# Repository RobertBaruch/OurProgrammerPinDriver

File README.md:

# OurProgrammerPinDriver
Pin driver schematic and PCB for OurProgrammer

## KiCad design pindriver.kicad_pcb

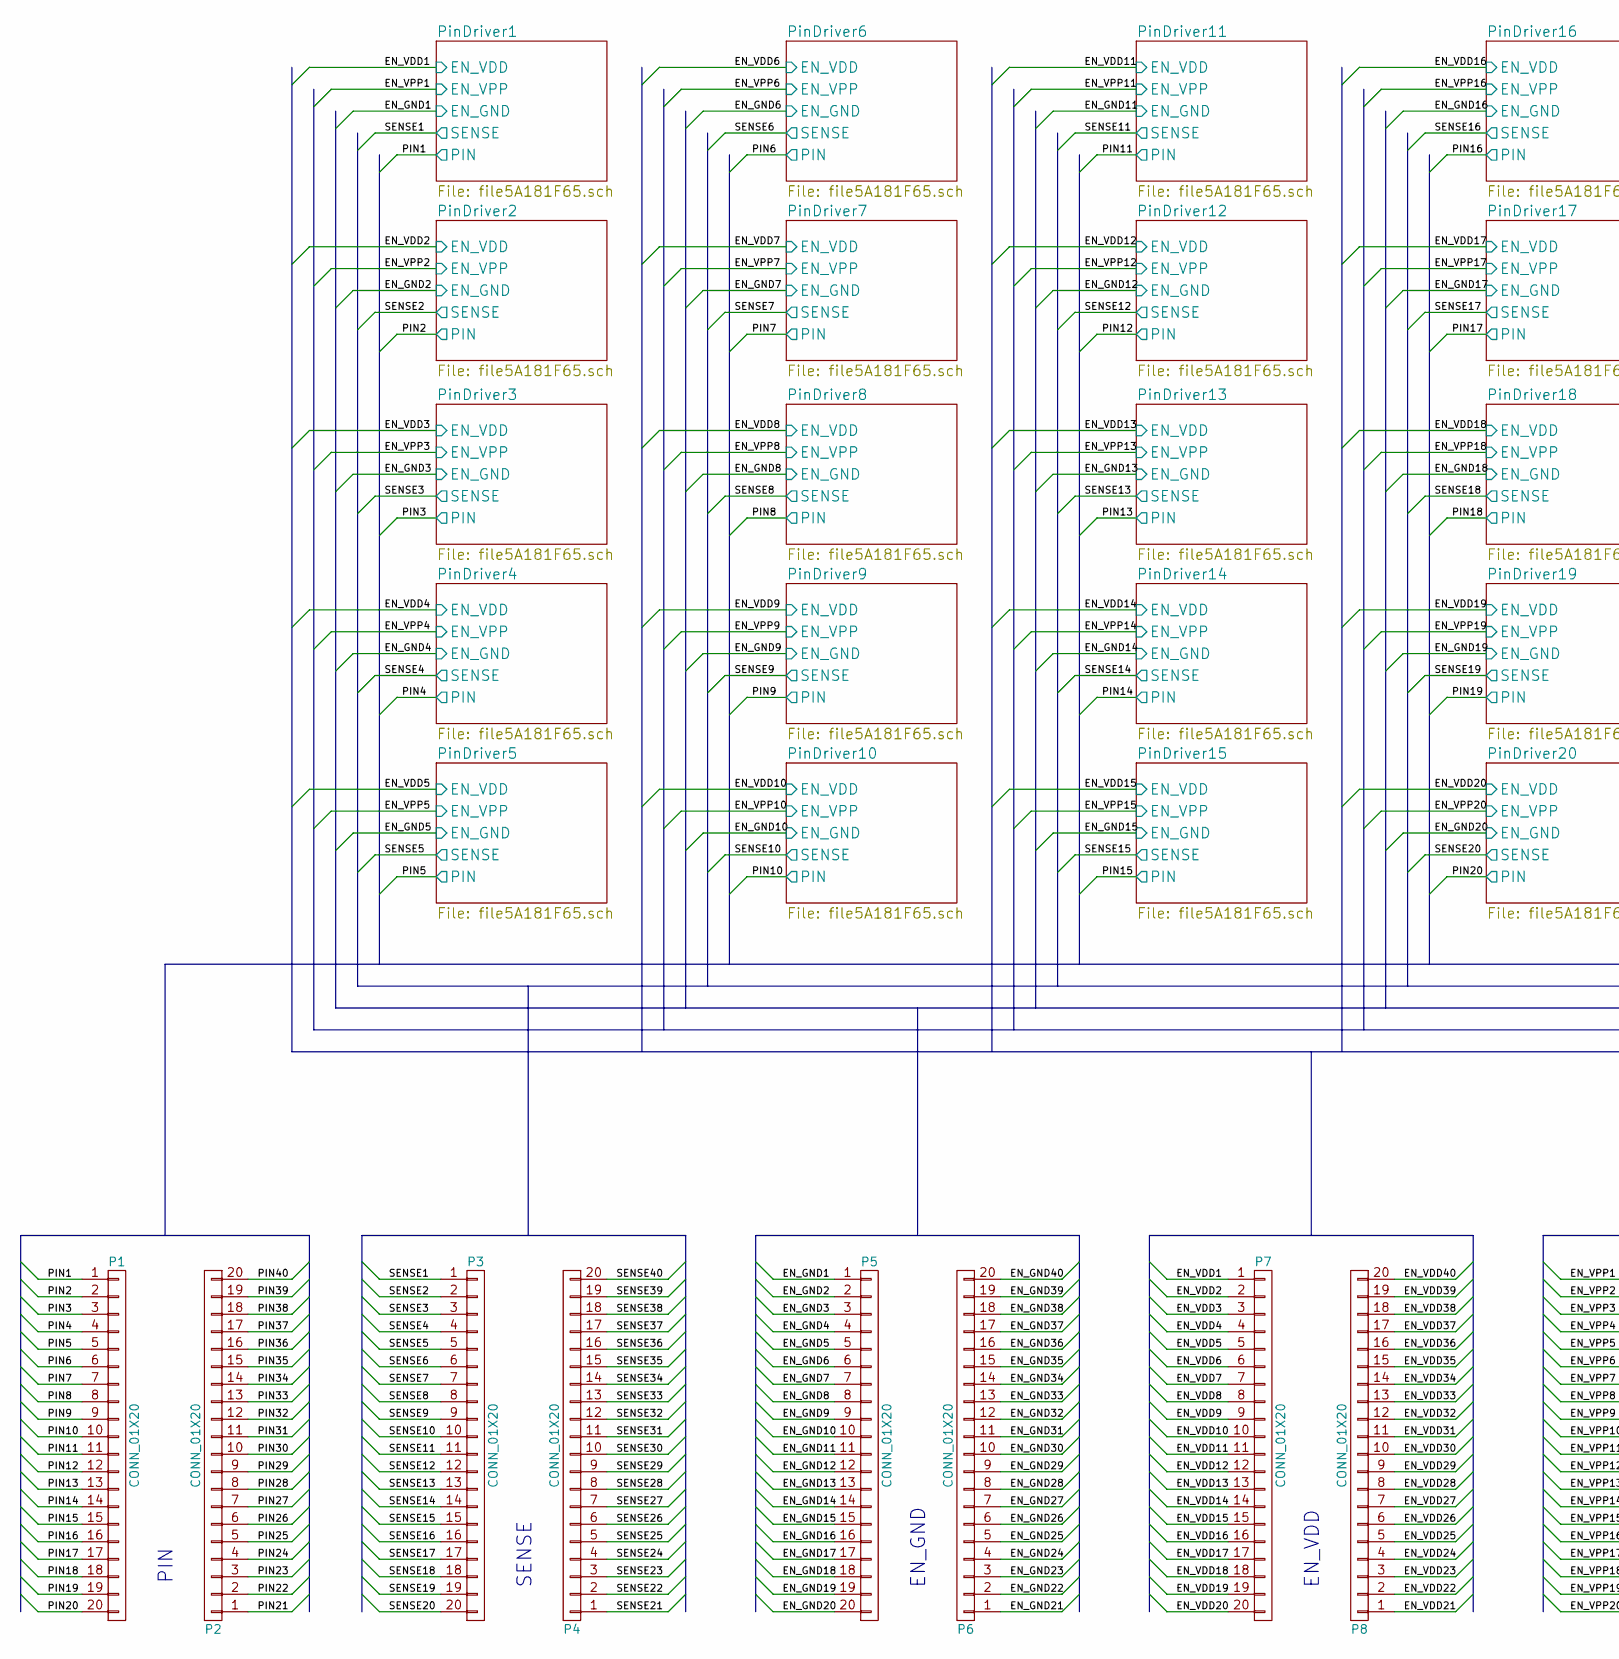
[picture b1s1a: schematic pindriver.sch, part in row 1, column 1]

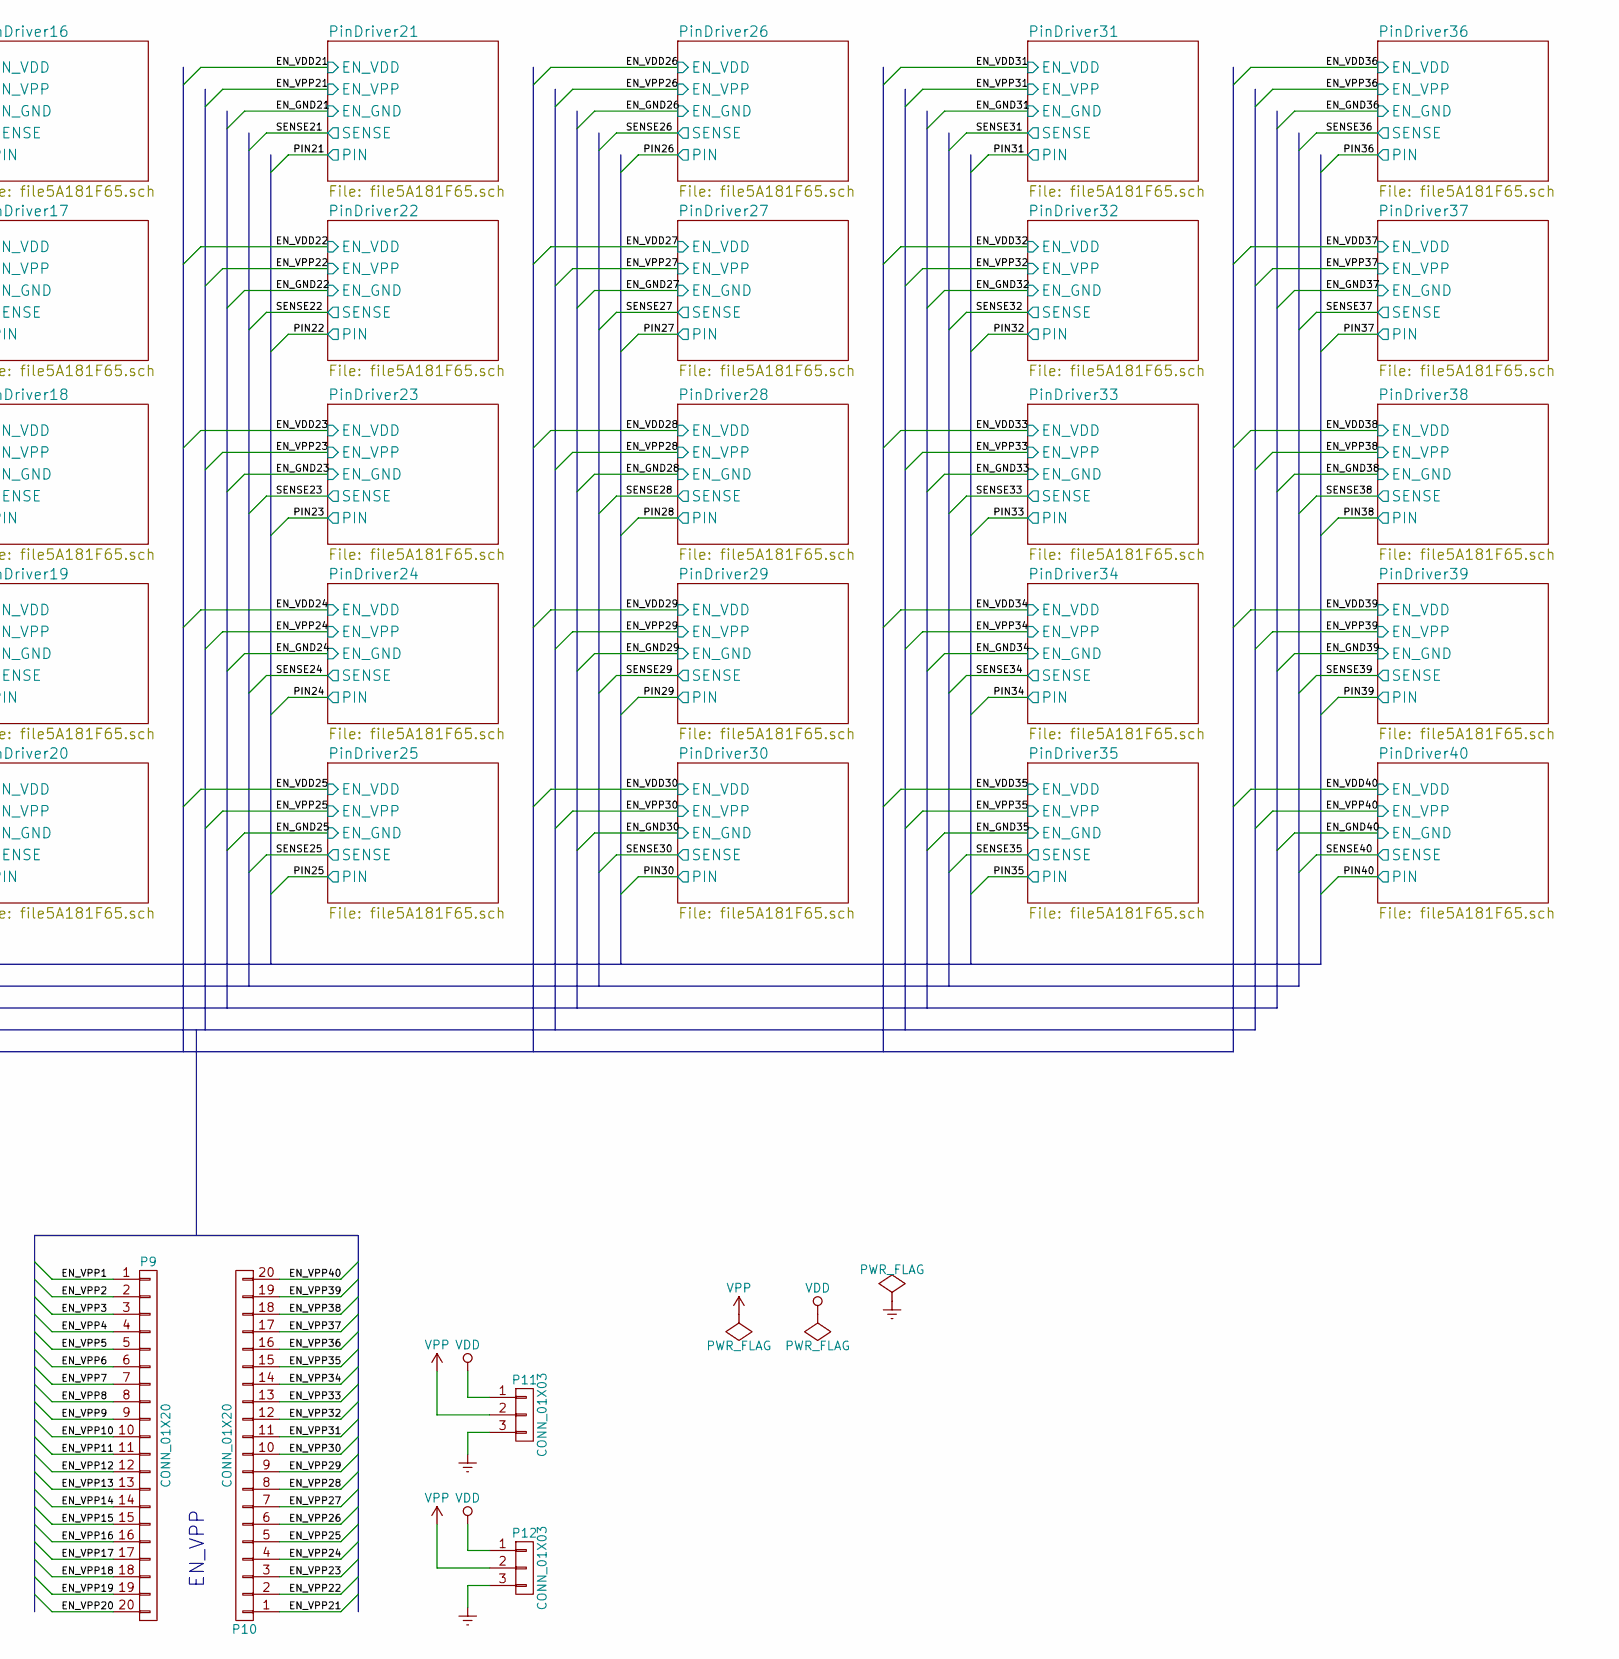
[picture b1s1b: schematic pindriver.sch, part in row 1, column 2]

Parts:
P1, P2, P3, P4, P5, P6, P7, P8, P9, P10: CONN_01X20; SL-120-X-XX_1x20
P11, P12: CONN_01X03; SL-103-X-XX_1x03

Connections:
/EN_GND1: P5.1; also elsewhere on the board
/EN_GND2: P5.2; also elsewhere on the board
/EN_GND3: P5.3; also elsewhere on the board
/EN_GND4: P5.4; also elsewhere on the board
/EN_GND5: P5.5; also elsewhere on the board
/EN_GND6: P5.6; also elsewhere on the board
/EN_GND7: P5.7; also elsewhere on the board
/EN_GND8: P5.8; also elsewhere on the board
/EN_GND9: P5.9; also elsewhere on the board
/EN_GND10: P5.10; also elsewhere on the board
/EN_GND11: P5.11; also elsewhere on the board
/EN_GND12: P5.12; also elsewhere on the board
/EN_GND13: P5.13; also elsewhere on the board
/EN_GND14: P5.14; also elsewhere on the board
/EN_GND15: P5.15; also elsewhere on the board
/EN_GND16: P5.16; also elsewhere on the board
/EN_GND17: P5.17; also elsewhere on the board
/EN_GND18: P5.18; also elsewhere on the board
/EN_GND19: P5.19; also elsewhere on the board
/EN_GND20: P5.20; also elsewhere on the board
/EN_GND21: P6.1; also elsewhere on the board
/EN_GND22: P6.2; also elsewhere on the board
/EN_GND23: P6.3; also elsewhere on the board
/EN_GND24: P6.4; also elsewhere on the board
/EN_GND25: P6.5; also elsewhere on the board
/EN_GND26: P6.6; also elsewhere on the board
/EN_GND27: P6.7; also elsewhere on the board
/EN_GND28: P6.8; also elsewhere on the board
/EN_GND29: P6.9; also elsewhere on the board
/EN_GND30: P6.10; also elsewhere on the board
/EN_GND31: P6.11; also elsewhere on the board
/EN_GND32: P6.12; also elsewhere on the board
/EN_GND33: P6.13; also elsewhere on the board
/EN_GND34: P6.14; also elsewhere on the board
/EN_GND35: P6.15; also elsewhere on the board
/EN_GND36: P6.16; also elsewhere on the board
/EN_GND37: P6.17; also elsewhere on the board
/EN_GND38: P6.18; also elsewhere on the board
/EN_GND39: P6.19; also elsewhere on the board
/EN_GND40: P6.20; also elsewhere on the board
/EN_VDD1: P7.1; also elsewhere on the board
/EN_VDD2: P7.2; also elsewhere on the board
/EN_VDD3: P7.3; also elsewhere on the board
/EN_VDD4: P7.4; also elsewhere on the board
/EN_VDD5: P7.5; also elsewhere on the board
/EN_VDD6: P7.6; also elsewhere on the board
/EN_VDD7: P7.7; also elsewhere on the board
/EN_VDD8: P7.8; also elsewhere on the board
/EN_VDD9: P7.9; also elsewhere on the board
/EN_VDD10: P7.10; also elsewhere on the board
/EN_VDD11: P7.11; also elsewhere on the board
/EN_VDD12: P7.12; also elsewhere on the board
/EN_VDD13: P7.13; also elsewhere on the board
/EN_VDD14: P7.14; also elsewhere on the board
/EN_VDD15: P7.15; also elsewhere on the board
/EN_VDD16: P7.16; also elsewhere on the board
/EN_VDD17: P7.17; also elsewhere on the board
/EN_VDD18: P7.18; also elsewhere on the board
/EN_VDD19: P7.19; also elsewhere on the board
/EN_VDD20: P7.20; also elsewhere on the board
/EN_VDD21: P8.1; also elsewhere on the board
/EN_VDD22: P8.2; also elsewhere on the board
/EN_VDD23: P8.3; also elsewhere on the board
/EN_VDD24: P8.4; also elsewhere on the board
/EN_VDD25: P8.5; also elsewhere on the board
/EN_VDD26: P8.6; also elsewhere on the board
/EN_VDD27: P8.7; also elsewhere on the board
/EN_VDD28: P8.8; also elsewhere on the board
/EN_VDD29: P8.9; also elsewhere on the board
/EN_VDD30: P8.10; also elsewhere on the board
/EN_VDD31: P8.11; also elsewhere on the board
/EN_VDD32: P8.12; also elsewhere on the board
/EN_VDD33: P8.13; also elsewhere on the board
/EN_VDD34: P8.14; also elsewhere on the board
/EN_VDD35: P8.15; also elsewhere on the board
/EN_VDD36: P8.16; also elsewhere on the board
/EN_VDD37: P8.17; also elsewhere on the board
/EN_VDD38: P8.18; also elsewhere on the board
/EN_VDD39: P8.19; also elsewhere on the board
/EN_VDD40: P8.20; also elsewhere on the board
/EN_VPP1: P9.1; also elsewhere on the board
/EN_VPP2: P9.2; also elsewhere on the board
/EN_VPP3: P9.3; also elsewhere on the board
/EN_VPP4: P9.4; also elsewhere on the board
/EN_VPP5: P9.5; also elsewhere on the board
/EN_VPP6: P9.6; also elsewhere on the board
/EN_VPP7: P9.7; also elsewhere on the board
/EN_VPP8: P9.8; also elsewhere on the board
/EN_VPP9: P9.9; also elsewhere on the board
/EN_VPP10: P9.10; also elsewhere on the board
/EN_VPP11: P9.11; also elsewhere on the board
/EN_VPP12: P9.12; also elsewhere on the board
/EN_VPP13: P9.13; also elsewhere on the board
/EN_VPP14: P9.14; also elsewhere on the board
/EN_VPP15: P9.15; also elsewhere on the board
/EN_VPP16: P9.16; also elsewhere on the board
/EN_VPP17: P9.17; also elsewhere on the board
/EN_VPP18: P9.18; also elsewhere on the board
/EN_VPP19: P9.19; also elsewhere on the board
/EN_VPP20: P9.20; also elsewhere on the board
/EN_VPP21: P10.1; also elsewhere on the board
/EN_VPP22: P10.2; also elsewhere on the board
/EN_VPP23: P10.3; also elsewhere on the board
/EN_VPP24: P10.4; also elsewhere on the board
/EN_VPP25: P10.5; also elsewhere on the board
/EN_VPP26: P10.6; also elsewhere on the board
/EN_VPP27: P10.7; also elsewhere on the board
/EN_VPP28: P10.8; also elsewhere on the board
/EN_VPP29: P10.9; also elsewhere on the board
/EN_VPP30: P10.10; also elsewhere on the board
/EN_VPP31: P10.11; also elsewhere on the board
/EN_VPP32: P10.12; also elsewhere on the board
/EN_VPP33: P10.13; also elsewhere on the board
/EN_VPP34: P10.14; also elsewhere on the board
/EN_VPP35: P10.15; also elsewhere on the board
/EN_VPP36: P10.16; also elsewhere on the board
/EN_VPP37: P10.17; also elsewhere on the board
/EN_VPP38: P10.18; also elsewhere on the board
/EN_VPP39: P10.19; also elsewhere on the board
/EN_VPP40: P10.20; also elsewhere on the board
/PIN1: P1.1; also elsewhere on the board
/PIN2: P1.2; also elsewhere on the board
/PIN3: P1.3; also elsewhere on the board
/PIN4: P1.4; also elsewhere on the board
/PIN5: P1.5; also elsewhere on the board
/PIN6: P1.6; also elsewhere on the board
/PIN7: P1.7; also elsewhere on the board
/PIN8: P1.8; also elsewhere on the board
/PIN9: P1.9; also elsewhere on the board
/PIN10: P1.10; also elsewhere on the board
/PIN11: P1.11; also elsewhere on the board
/PIN12: P1.12; also elsewhere on the board
/PIN13: P1.13; also elsewhere on the board
/PIN14: P1.14; also elsewhere on the board
/PIN15: P1.15; also elsewhere on the board
/PIN16: P1.16; also elsewhere on the board
/PIN17: P1.17; also elsewhere on the board
/PIN18: P1.18; also elsewhere on the board
/PIN19: P1.19; also elsewhere on the board
/PIN20: P1.20; also elsewhere on the board
/PIN21: P2.1; also elsewhere on the board
/PIN22: P2.2; also elsewhere on the board
/PIN23: P2.3; also elsewhere on the board
/PIN24: P2.4; also elsewhere on the board
/PIN25: P2.5; also elsewhere on the board
/PIN26: P2.6; also elsewhere on the board
/PIN27: P2.7; also elsewhere on the board
/PIN28: P2.8; also elsewhere on the board
/PIN29: P2.9; also elsewhere on the board
/PIN30: P2.10; also elsewhere on the board
/PIN31: P2.11; also elsewhere on the board
/PIN32: P2.12; also elsewhere on the board
/PIN33: P2.13; also elsewhere on the board
/PIN34: P2.14; also elsewhere on the board
/PIN35: P2.15; also elsewhere on the board
/PIN36: P2.16; also elsewhere on the board
/PIN37: P2.17; also elsewhere on the board
/PIN38: P2.18; also elsewhere on the board
/PIN39: P2.19; also elsewhere on the board
/PIN40: P2.20; also elsewhere on the board
/SENSE1: P3.1; also elsewhere on the board
/SENSE2: P3.2; also elsewhere on the board
/SENSE3: P3.3; also elsewhere on the board
/SENSE4: P3.4; also elsewhere on the board
/SENSE5: P3.5; also elsewhere on the board
/SENSE6: P3.6; also elsewhere on the board
/SENSE7: P3.7; also elsewhere on the board
/SENSE8: P3.8; also elsewhere on the board
/SENSE9: P3.9; also elsewhere on the board
/SENSE10: P3.10; also elsewhere on the board
/SENSE11: P3.11; also elsewhere on the board
/SENSE12: P3.12; also elsewhere on the board
/SENSE13: P3.13; also elsewhere on the board
/SENSE14: P3.14; also elsewhere on the board
/SENSE15: P3.15; also elsewhere on the board
/SENSE16: P3.16; also elsewhere on the board
/SENSE17: P3.17; also elsewhere on the board
/SENSE18: P3.18; also elsewhere on the board
/SENSE19: P3.19; also elsewhere on the board
/SENSE20: P3.20; also elsewhere on the board
/SENSE21: P4.1; also elsewhere on the board
/SENSE22: P4.2; also elsewhere on the board
/SENSE23: P4.3; also elsewhere on the board
/SENSE24: P4.4; also elsewhere on the board
/SENSE25: P4.5; also elsewhere on the board
/SENSE26: P4.6; also elsewhere on the board
/SENSE27: P4.7; also elsewhere on the board
/SENSE28: P4.8; also elsewhere on the board
/SENSE29: P4.9; also elsewhere on the board
/SENSE30: P4.10; also elsewhere on the board
/SENSE31: P4.11; also elsewhere on the board
/SENSE32: P4.12; also elsewhere on the board
/SENSE33: P4.13; also elsewhere on the board
/SENSE34: P4.14; also elsewhere on the board
/SENSE35: P4.15; also elsewhere on the board
/SENSE36: P4.16; also elsewhere on the board
/SENSE37: P4.17; also elsewhere on the board
/SENSE38: P4.18; also elsewhere on the board
/SENSE39: P4.19; also elsewhere on the board
/SENSE40: P4.20; also elsewhere on the board
GNDREF: P11.3, P12.3; also elsewhere on the board
VDD: P11.1, P12.1; also elsewhere on the board
VPP: P11.2, P12.2; also elsewhere on the board

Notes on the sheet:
PIN
SENSE
EN_GND
EN_VDD
EN_VPP
